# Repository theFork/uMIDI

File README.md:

```
       __  __ _____ _____ _____
      |  \/  |_   _|  __ \_   _|
 _   _| \  / | | | | |  | || |
| | | | |\/| | | | | |  | || |
| |_| | |  | |_| |_| |__| || |_
|  _,_|_|  |_|_____|_____/_____|
| |
|_|
```

The swiss army knife for quick and easy developement of MIDI applications. Possible applications are everything that uses MIDI.

# Documentation
Documentation of hard- and software can be found at https://thefork.github.io/uMIDI/.

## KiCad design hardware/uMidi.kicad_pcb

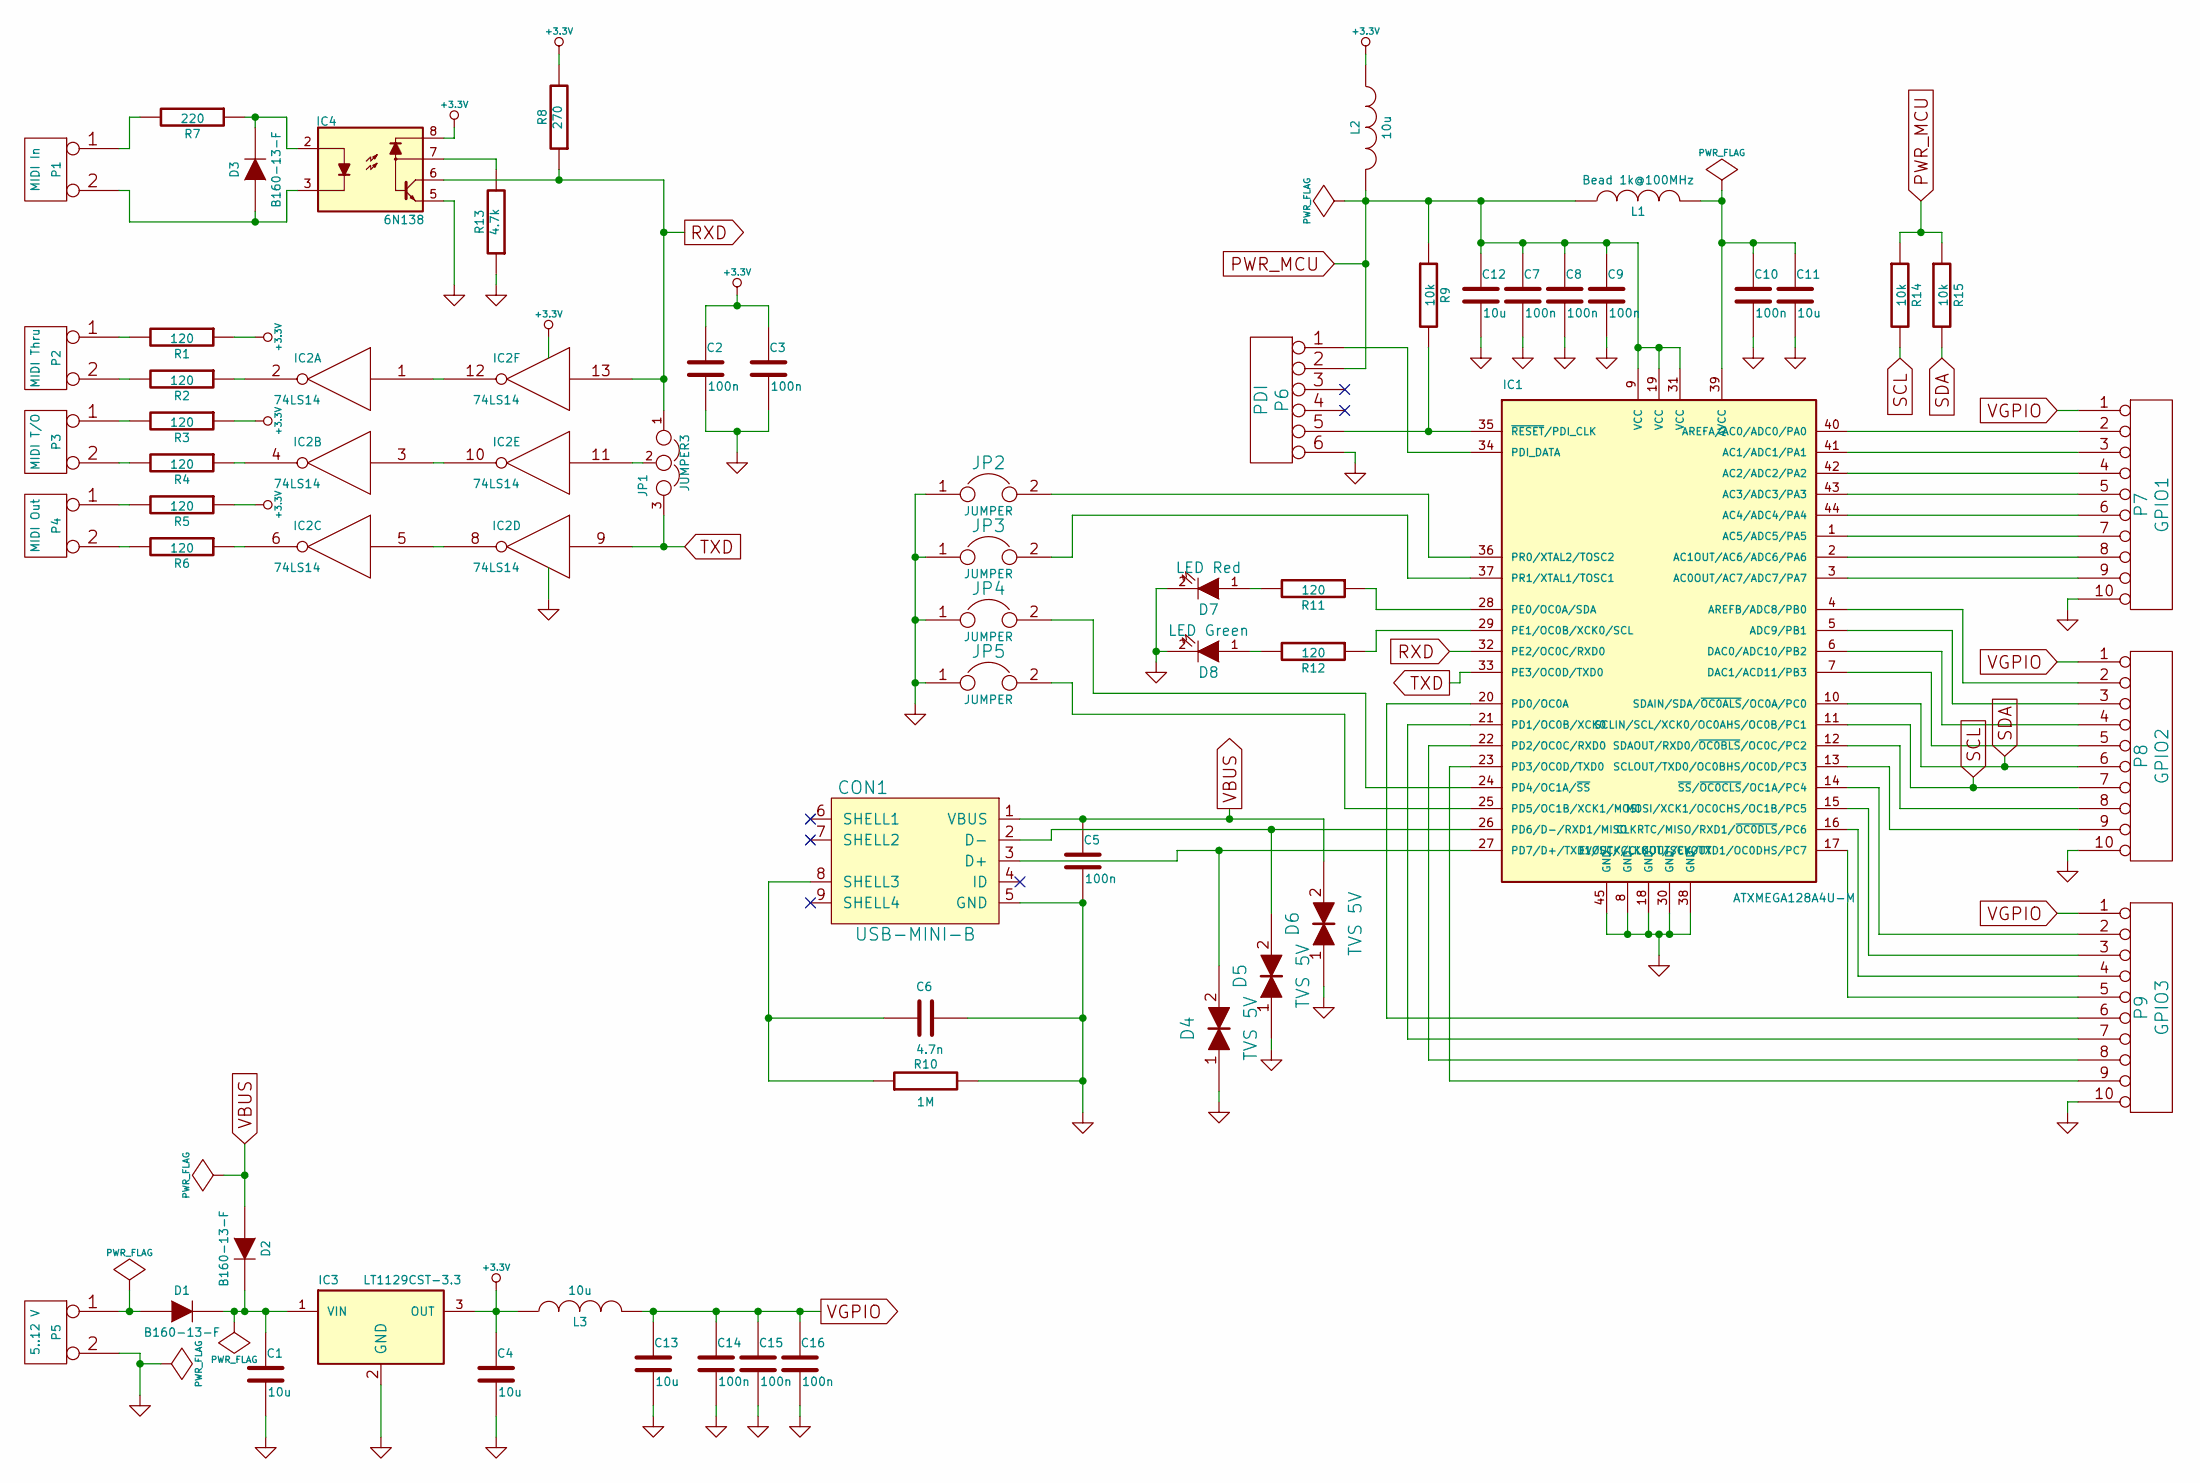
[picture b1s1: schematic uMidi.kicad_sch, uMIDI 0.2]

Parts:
C1, C4, C11, C12, C13: 10u; C_0603; Manufacturer Part Number C0603C106M9PACTU
C2, C3, C5, C7, C8, C9, C10, C14, C15, C16: 100n; C_0603; Manufacturer Part Number CL10B104KB8NNNC
C6: 4.7n; C_0603; Manufacturer Part Number GRM188R71H472KA01D
CON1: USB-MINI-B; Manufacturer Part Number UX60-MB-5ST
D1, D2, D3: B160-13-F; DI-214-AC_SMA; Manufacturer Part Number B160-13-F
D4, D5, D6: TVS 5V; C_0603; Manufacturer Part Number CPDU5V0
D7: LED Red; Manufacturer Part Number LTST-C191KRKT
D8: LED Green; Manufacturer Part Number LTST-C191KGKT
IC1: ATXMEGA128A4U-M; QFN-44-1EP; Manufacturer Part Number ATXMEGA128A4U-MH
IC2: 74LS14; Manufacturer Part Number 74LVT14D,118
IC3: LT1129CST-3.3; SOT-223; Manufacturer Part Number LT1129CST-3.3#PBF
IC4: 6N138; Optocoupler_DIP8_SMD; Manufacturer Part Number 6N138S-TA1
JP1: JUMPER3
JP2, JP3, JP4, JP5: JUMPER
L1: Bead 1k@100MHz; C_0603; Manufacturer Part Number BLM18RK102SN1D
L2, L3: 10u; C_0603; Manufacturer Part Number GLFR1608T100M-LR
P1: MIDI In
P2: MIDI Thru
P3: MIDI T/O
P4: MIDI Out
P5: 5..12 V
P6: PDI; Manufacturer Part Number 67996-206HLF
P7: GPIO1; VASCH5x2; Manufacturer Part Number 30310-6002HB
P8: GPIO2; VASCH5x2; Manufacturer Part Number 30310-6002HB
P9: GPIO3; VASCH5x2; Manufacturer Part Number 30310-6002HB
R1, R2, R3, R4, R5, R6, R11, R12: 120; R_0603; Manufacturer Part Number ERJ-3GEYJ121V
R7: 220; R_0603; Manufacturer Part Number ERJ-3GEYJ221V
R8: 270; R_0603; Manufacturer Part Number ERJ-3GEYJ271V
R9, R14, R15: 10k; R_0603; Manufacturer Part Number ERJ-3GEYJ103V
R10: 1M; R_0603; Manufacturer Part Number ERJ-3GEYJ105V
R13: 4.7k; R_0603; Manufacturer Part Number ERJ-3GEYJ472V

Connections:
+3.3V: C2.1, C3.1, C4.1, IC2.14 (VCC), IC3.3 (OUT), IC4.8, L2.1, L3.1, R1.1, R3.1, R5.1, R8.2
GND: C1.2, C2.2, C3.2, C4.2, C5.2, C6.1, C7.2, C8.2, C9.2, C10.2, C11.2, C12.2, C13.2, C14.2, C15.2, C16.2, CON1.5 (GND), D4.1, D5.1, D6.1, D7.2 (K), D8.2 (K), IC1.8 (GND), IC1.18 (GND), IC1.30 (GND), IC1.38 (GND), IC1.45 (GND), IC2.7 (GND), IC3.2 (GND), IC3.4 (GNDPAD), IC4.5, JP2.1, JP3.1, JP4.1, JP5.1, P5.2 (PM), P6.6, P7.10, P8.10, P9.10, R10.2, R13.1; also elsewhere on the board
unnamed: C1.1, D1.2 (K), D2.2 (K), IC3.1 (VIN)
unnamed: C6.2, CON1.8 (SHELL3), R10.1
unnamed: C10.1, C11.1, IC1.39 (AVCC), L1.2
unnamed: CON1.2 (D-), D5.2, IC1.26 (PD6/D-/RXD1/MISO)
unnamed: CON1.3 (D+), D4.2, IC1.27 (PD7/D+/TXD1/SCK/CLKOUT/EVOUT)
unnamed: D1.1 (A), P5.1
unnamed: D3.1 (A), IC4.3, P1.2 (PM)
unnamed: D3.2 (K), IC4.2, R7.1
unnamed: D7.1 (A), R11.2
unnamed: D8.1 (A), R12.2
unnamed: IC1.1 (AC5/ADC5/PA5), P7.7
unnamed: IC1.2 (AC1OUT/AC6/ADC6/PA6), P7.8
unnamed: IC1.3 (AC0OUT/AC7/ADC7/PA7), P7.9
unnamed: IC1.4 (AREFB/ADC8/PB0), P8.2
unnamed: IC1.5 (ADC9/PB1), P8.3
unnamed: IC1.6 (DAC0/ADC10/PB2), P8.4
unnamed: IC1.7 (DAC1/ACD11/PB3), P8.5
unnamed: IC1.12 (SDAOUT/RXD0/~OC0BLS/OC0C/PC2), P8.8
unnamed: IC1.13 (SCLOUT/TXD0/OC0BHS/OC0D/PC3), P8.9
unnamed: IC1.14 (~SS/~OC0CLS/OC1A/PC4), P9.2
unnamed: IC1.15 (MOSI/XCK1/OC0CHS/OC1B/PC5), P9.3
unnamed: IC1.16 (CLKRTC/MISO/RXD1/~OC0DLS/PC6), P9.4
unnamed: IC1.17 (EVOUT/CLKOUT/SCK/TXD1/OC0DHS/PC7), P9.5
unnamed: IC1.20 (PD0/OC0A), P9.6
unnamed: IC1.21 (PD1/OC0B/XCK0), P9.7
unnamed: IC1.22 (PD2/OC0C/RXD0), P9.8
unnamed: IC1.23 (PD3/OC0D/TXD0), P9.9
unnamed: IC1.24 (PD4/OC1A/~SS), JP4.2
unnamed: IC1.25 (PD5/OC1B/XCK1/MOSI), JP5.2
unnamed: IC1.28 (PE0/OC0A/SDA), R11.1
unnamed: IC1.29 (PE1/OC0B/XCK0/SCL), R12.1
unnamed: IC1.34 (PDI_DATA), P6.1
unnamed: IC1.35 (~RESET/PDI_CLK), P6.5, R9.2
unnamed: IC1.36 (PR0/XTAL2/TOSC2), JP2.2
unnamed: IC1.37 (PR1/XTAL1/TOSC1), JP3.2
unnamed: IC1.40 (AREFA/AC0/ADC0/PA0), P7.2
unnamed: IC1.41 (AC1/ADC1/PA1), P7.3
unnamed: IC1.42 (AC2/ADC2/PA2), P7.4
unnamed: IC1.43 (AC3/ADC3/PA3), P7.5
unnamed: IC1.44 (AC4/ADC4/PA4), P7.6
unnamed: IC2.1, IC2.12
unnamed: IC2.2, R2.1
unnamed: IC2.4, R4.1
unnamed: IC2.5, IC2.8
unnamed: IC2.6, R6.1
unnamed: IC2.3, IC2.10
unnamed: IC2.11, JP1.2
unnamed: IC4.7, R13.2
unnamed: P1.1, R7.2
unnamed: P2.1, R1.2
unnamed: P2.2 (PM), R2.2
unnamed: P3.1, R3.2
unnamed: P3.2 (PM), R4.2
unnamed: P4.1, R5.2
unnamed: P4.2 (PM), R6.2
PWR_MCU: C7.1, C8.1, C9.1, C12.1, IC1.9 (VCC), IC1.19 (VCC), IC1.31 (VCC), L1.1, L2.2, P6.2, R9.1, R14.1, R15.1
RXD: IC1.32 (PE2/OC0C/RXD0), IC2.13, IC4.6, JP1.1, R8.1
SCL: IC1.11 (SCLIN/SCL/XCK0/OC0AHS/OC0B/PC1), P8.7, R14.2
SDA: IC1.10 (SDAIN/SDA/~OC0ALS/OC0A/PC0), P8.6, R15.2
TXD: IC1.33 (PE3/OC0D/TXD0), IC2.9, JP1.3
VBUS: C5.1, CON1.1 (VBUS), D2.1 (A), D6.2
VGPIO: C13.1, C14.1, C15.1, C16.1, L3.2, P7.1, P8.1, P9.1

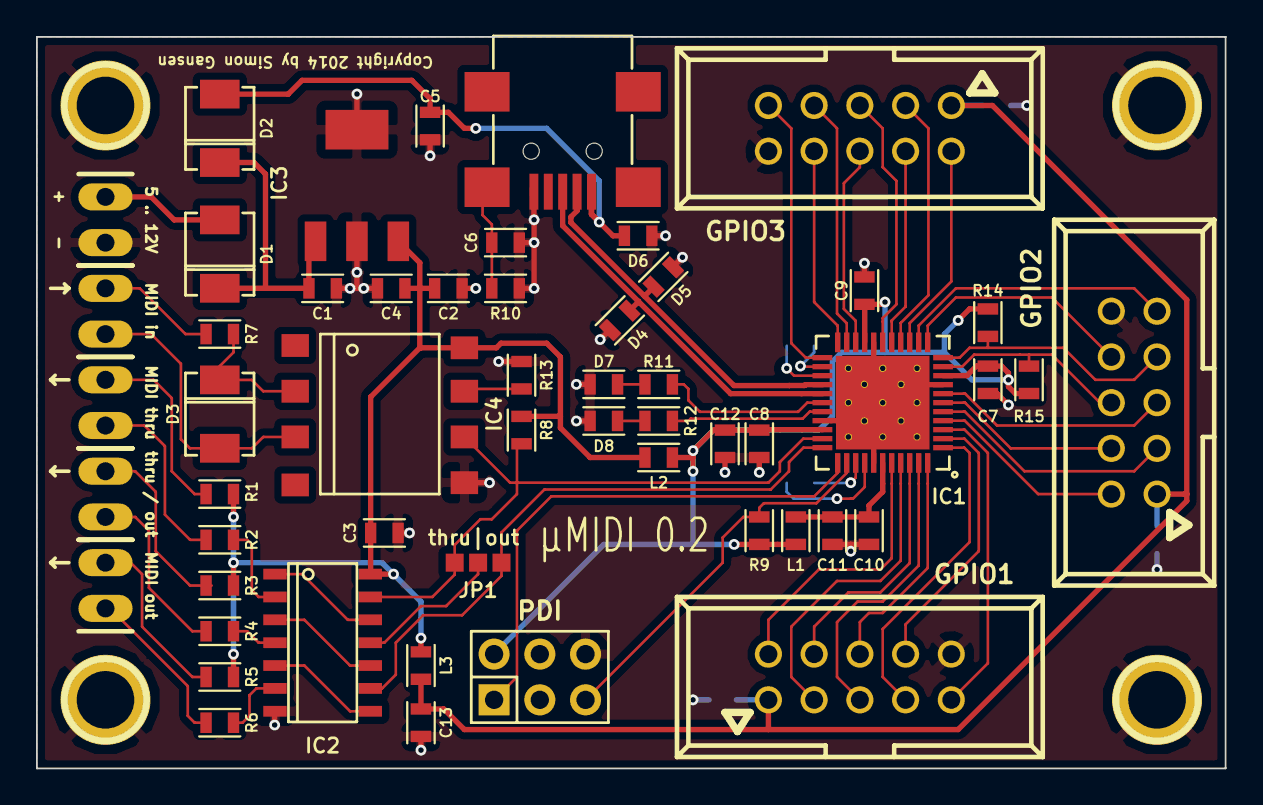
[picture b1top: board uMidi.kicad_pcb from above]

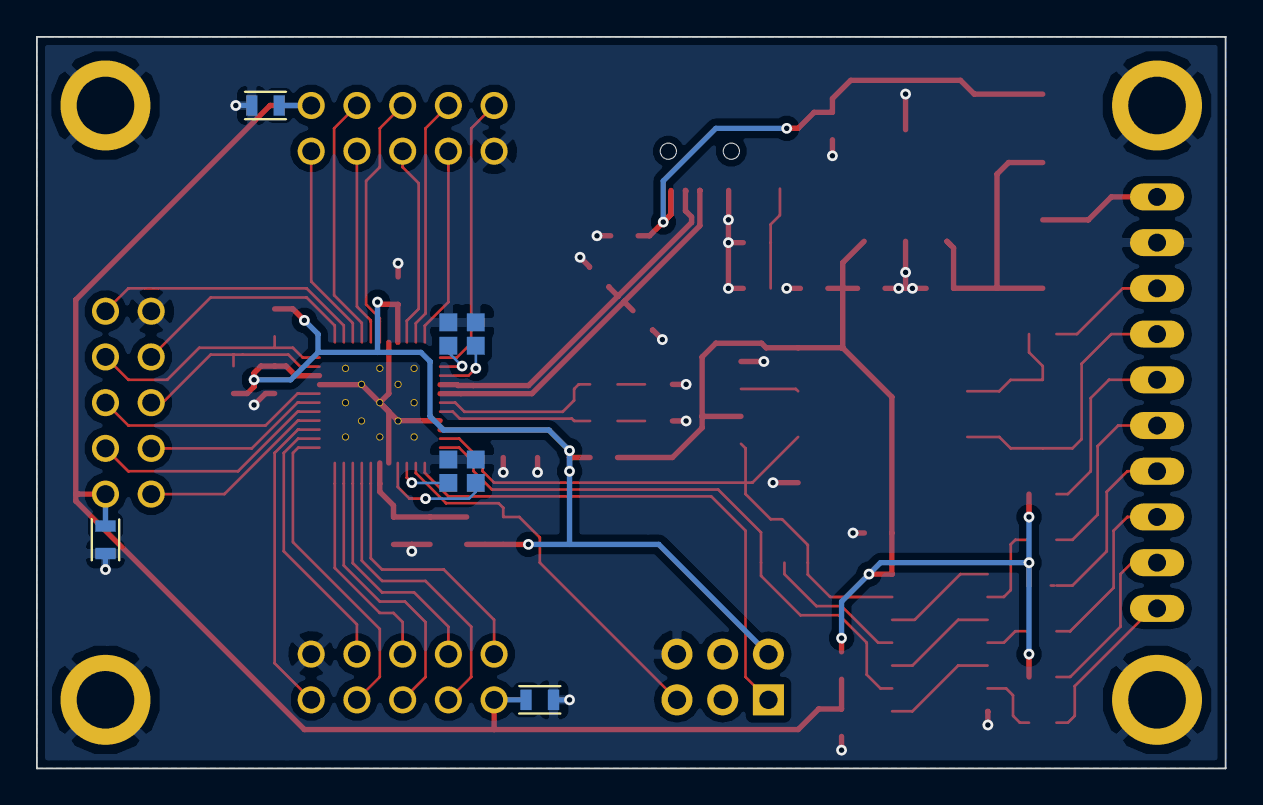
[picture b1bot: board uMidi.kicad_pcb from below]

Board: 2 copper layers, 66.0 x 40.6 mm, 65 parts (7 on the bottom side), 64 nets.

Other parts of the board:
1PIN, 1PIN#2, 1PIN#3, 1PIN#4: P***; 1pin

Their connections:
GND: 1PIN.1, 1PIN#2.1, 1PIN#3.1, 1PIN#4.1; also elsewhere on the board

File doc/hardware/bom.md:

# Bill of Material

## Semiconductors
| Name | Value              | Package       |
|------|--------------------|---------------|
| IC1  | ATXMEGA128A4U-M    | VQFN44        |
| IC2  | 74LS14             |               |
| IC3  | LT1129CST-3.3      | SOT-223       |
| IC4  | 6N138              | SMD-8         |
| D1   | DIODE              |               |
| D2   | DIODE              |               |
| D3   | DIODE              |               |
| D4   | TVS                | 0603          |
| D5   | TVS                | 0603          |
| D6   | TVS                | 0603          |
| D7   | LED, red           | 0603          |
| D8   | LED, green         | 0603          |

## Connectors
| Name | Type               |
|------|--------------------|
| CON1 | USB-MINI-B         |
| P6   | PDI                |
| P7   | GPIO1              |
| P8   | GPIO2              |
| P9   | GPIO2              |

## Passives
| Name | Value              | Package       |
|------|--------------------|---------------|
| R1   | 120                | 0603          |
| R2   | 120                | 0603          |
| R3   | 120                | 0603          |
| R4   | 120                | 0603          |
| R5   | 120                | 0603          |
| R6   | 120                | 0603          |
| R7   | 220                | 0603          |
| R8   | 270                | 0603          |
| R9   | 10k                | 0603          |
| R10  | 1M                 | 0603          |
| R11  | 120                | 0603          |
| R12  | 120                | 0603          |
| R13  | 4.7k               | 0603          |
| R14  | 10k                | 0603          |
| R15  | 10k                | 0603          |
| C1   | 10u                | 0603          |
| C2   | 100n               | 0603          |
| C3   | 100n               | 0603          |
| C4   | 10u                | 0603          |
| C5   | 100n               | 0603          |
| C6   | 4.7n               | 0603          |
| C7   | 100n               | 0603          |
| C8   | 100n               | 0603          |
| C9   | 100n               | 0603          |
| C10  | 100n               | 0603          |
| C11  | 10u                | 0603          |
| C12  | 10u                | 0603          |
| C13  | 10u                | 0603          |
| C14  | 100n               | 0603          |
| C15  | 100n               | 0603          |
| C16  | 100n               | 0603          |
| L1   | Bead               | 0603          |
| L2   | 10u                | 0603          |
| L3   | 10u                | 0603          |

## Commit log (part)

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2016-02-25 Add doxygen software documentation skeleton
2016-02-26 Add missing fuse byte FUSEBYTE0 to Makefiles
2016-03-05 Remove unnecessary whitespace in global Makefile
2016-03-05 Remove unnecessary quotation marks from global Makefile
2016-03-05 Remove onboard LED command
2016-03-06 Complete doxygen mainpage (for now)
2016-03-06 Add initial doxygen documentation
2016-03-06 Remove led debugging; Fix typo; Add doxy comments
2016-03-06 Add switcher documentation page stub
2016-03-06 Add feedback to fwupdate target
2016-03-06 Improve readability of wave functions
2016-03-06 Add activity diagram of the waveform update task
2016-03-06 Implement USB control interface and tap tempo
2016-03-08 Improve GPIO API (see details)
    Applications now need only to provide GPIO pin type configurations for the pins
    they really need. Also there is a new function configure_gpio_pin() that allows
    configuration of pins apart from init_gpio_module().
2016-03-08 Adapt sequencer app to new GPIO API
2016-03-08 Adapt templates to new GPIO API
2016-03-08 Fix warnings in sequencer module due to GPIO API change
2016-03-08 Adapt switcher app to new GPIO API
2016-03-08 Brick sequencer app (see detailed commit message)
    When the GPIO inputs are not properly configured, the function poll_encoder(),
    which is registered as a background task, runs into an endless loop while trying
    to de-bounce the switch. This wakes up the watchdog, which then resets the MCU.
2016-03-12 Document struct jumpers
2016-03-12 Implement generic poll_gpio_input in GPIO module
2016-03-12 Make encoder module capable of handling multiple encoders
2016-03-12 Extract handling of encoder position changes to private function
2016-03-12 Make switch on encoders optional
2016-03-12 Implement HMI module
2016-03-12 Implement 4-phase encoder
2016-03-12 Add reset_wave() to wave module
2016-03-12 Use second encoder to start/stop and select the pattern
2016-03-13 Move wave patterns to program space
2016-03-13 Improve pattern 03
2016-03-13 Make "normal" waveforms accessible
2016-03-14 Generate software version ID string and print it out with the help command
2016-03-14 Refactor sequencer stuff out out whammy app and wave module
2016-03-15 Fix input switch polling
2016-03-16 Clean up sequencer module and fix build
2016-03-16 Roughly specify switcher software
2016-03-19 Prepare for generalized leds
2016-03-19 Implement register_led function
2016-03-19 Fix USB application template
2016-03-19 Convert led.pin to a pointer to a GPIO pin
2016-03-19 Implement flashing save LED on program change
2016-03-19 Implement two blinks on unkown packages and updaet spec
2016-03-19 Implement save switch
2016-03-19 Fix warnings
2016-03-26 Remove datasheets and manuals
2016-03-26 Restructure documentation
2016-03-26 Finish first version of MIDI pinout spec
2016-03-26 Update documentation
2016-03-27 Implement generic send_midi_message()
2016-03-27 Implement proof-of-concept for generalized patterns
2016-03-27 Fix documentation of update_wave()
2016-03-27 Complete implementation of static single-channel sequencer
2016-03-27 Prepare API for multi-channel sequencing
2016-03-27 Remove factory-defined patterns from sequencer module
    These are application-specific and should thus be defined in application code,
    not the library. The Whammy note enumeration is also application-specific and
    therefore moved to the whammy application code as well.
2016-03-27 Implement sequencer clock tick callback
2016-03-27 Move sequencer patterns to EEPROM
2016-03-27 Implement pattern restore from hex-string
2016-03-28 Fix update page size computation
2016-03-28 Wait 2 seconds before saving a program
2016-03-28 Increase verbosity
2016-03-28 Implement export function for programs
2016-03-28 Increase size of serial command buffer
2016-03-28 serial_communication: Use usb_puts() where possible
    This fixes or rather circumvents a bug: When a command in the history is too
    long (larger than about 70 characters) usb_printf() crashes the firmware for
    unknown reasons. Using puts() instead seems to work perfectly fine.
2016-03-28 Implement backup and restore commands
2016-04-03 Fix on-board LEDs
2016-04-03 program.c: Remove debug code from program import
2016-04-03 Completely revert command line-editing "fix"
2016-04-03 Rename program_data.word -> program_data.dword
2016-04-03 Initialize program module with invalid [sic] program number
2016-04-03 Implement sanity checks and return value for import_bank()
2016-04-18 Handle velocity of note off/on messages
2016-04-21 Add a script that creates a full dump of the device
2016-04-21 Modify fuses to enable brown-out detection
2016-04-30 Prepare program_data struct
2016-04-30 Generalize kill-switch; Document program storage
2016-04-30 Handle note messages and toggle selected outputs
2016-04-30 Specify kill switch feature
2016-04-30 Fix program_data raw representation
2016-04-30 Prepare toggle output serial command
2016-04-30 Call note_off handler if velocity is zero
2016-04-30 Tweak wah range once again
2016-04-30 Sort wah module code
2016-04-30 Implement MIDI note on / off command handling
2016-04-30 Disable flashing of red LED on MIDI RX
2016-04-30 Fill in missing MIDI configs in all apps
2016-05-05 Add static power LED
2016-05-05 Refactor status LED: Use LED API
2016-05-06 Fix TX/RX typo; Reduce minimum current requirement
2016-05-07 Fix comment and indentation
2016-05-07 Modify power over midi spec
2016-05-19 serial_communication: Fix memory leak in exec_help
2016-05-20 Add copy and wipe functions for sequencer patterns
2016-05-20 Check if patterns change before writing to EEPROM
2016-05-20 Implement sequencer pattern modification API
2016-05-25 Disable interrupts during ADC offset calibration
2016-05-25 Add linear scaling function int -> midi_value_t
    Also uses fixed point arithmetic for computation of both directions.
2016-05-25 Improve calibration and implement EEPROM storage
2016-05-25 Adapt wah application to changes in the math API
2016-06-24 Cosmetics in main.c of templates
2016-06-25 Implement SPI bit-banging module
2016-06-26 Improve doc on background tasks
2016-06-28 Fix rogue pointer in print_command_from_history()
2016-07-23 Do not overwrite command history with empty lines
2016-07-23 serial_communication: Use simple strtok in exec_help()
2016-07-23 Move lookup tables to program space
2016-07-23 Shrink command history to four commands
2016-07-23 Only transmit CC if status LED is on
2016-07-24 Fix doxygen complaints about supposedly undefined yet documented symbols
2016-07-24 Fix ADC register array
2016-07-25 ADC: Incorporate ADC sample -> MIDI value conversion for ADC channel 0
2016-07-25 Switch to built-in ADC sample -> MIDI value conversion
2016-07-25 Add project-specific vimrc with some settings for the syntastic plugin
2016-11-17 Assign missing footprint
2016-11-17 Swap red and green LEDs according to doc
2016-12-29 HMI: Differentiate between short and long button press events
2016-12-29 program.h: Fix code example
2016-12-29 wave.h: Cosmetics
2016-12-29 Add adjust_program() to program module
2016-12-29 Add program update service function to program module
2016-12-30 config.c: Use MIDI channel enum values
2016-12-30 whammy.c: Make global variables static
2016-12-30 Add factory reset command
2016-12-30 Implement sequencer mode toggle
2016-12-30 Add CLI for pattern modification
2016-12-30 Implement program storage
2016-12-30 Add type definitions for whammy controller program storage
2016-12-30 Handle MIDI program change messages
2016-12-30 Expand dump command to programs
2016-12-30 Expand speed adjustment to all control modes
2016-12-30 Restructure HMI
2016-12-30 Remove obsolete tap tempo button callback
2016-12-30 Implement whammy mode selection
2016-12-30 Do not load a program at startup
2016-12-30 Implement static detune mode
2016-12-30 Implement program selection
2016-12-30 Add ability to update the current program via command line
2017-01-01 Add MIDI sniffer application
2017-01-01 Implement serial command to select the MIDI channel to sniff on
2017-01-01 Remove GPIO configuration
2017-01-01 Explicitly print out USART receiver errors
2017-01-01 Add LED matrix module
2017-01-01 Use LED bar graph module
2017-01-01 Use LED matrix module
2017-01-01 Refactor common stuff out of adafruit display modules
2017-02-25 Divide et impera
    Split the rather huge whammmy module into separate files for the UI (console,
    encoders/buttons and LEDs) and whammy control.
2017-02-25 Use LED matrix instead of HMI LEDs
2017-02-25 Implement display of the program number
2017-02-25 led_matrix: Implement bitmap display helper
2017-02-25 Indicate last changed setting
2017-03-30 Move character display code to LED matrix module
2017-03-30 Re-introduce HMI layers for pattern manipulation
2017-03-30 Separate CLI implementation from main user interface
2017-03-30 Implement pattern length manipulation
2017-03-30 Refactor state variable names
2017-03-30 Implement program copy and wipe
2017-03-30 Add normal and limit mode
2017-03-30 Add possibility to configure interrupts for HMI buttons
2017-03-30 Make use of safe callback wrapper where possible
2017-03-30 Fix background task frequency
2017-03-30 Fix template-nousb build
2017-11-04 Implement command to set the MIDI channel for CC messages
2018-01-22 TESTME: Implement pitch bend mode proof-of-concept
2018-01-22 TESTME: Use shiny new lit buttons
2018-01-22 Always read current setting before flushing the display
2018-01-22 Indicate various events with status LEDs
2018-01-22 Extract MIDI handling routines to separate module
2018-10-28 Generalize PWM module
2018-10-28 Add Wah functionality to Whammy controller
2020-03-26 Tweak syntastic compiler flags
2020-03-26 Configure GitLab CI
2020-03-26 Foward MIDI messages
2021-06-28 Adapt enable switch logic to momentary switch
2022-07-15 LED Matrix: Send buffer only if something has changed
2022-07-15 Improve character Q
2022-07-15 Sequencer: Add manual step function
2022-07-15 impr(Makefile): Nicer software ID for git tags
2022-08-26 Fix missing newlines and typo in docs
2024-04-30 Introduce two foot-switchable modes
2024-04-30 Clarify, that led.h is also useful for external LEDs
2024-04-30 Add cli command for getting both ctrl numbers at once
2024-04-30 chore(switcher): Fix warnings; cosmetics
2024-05-01 chore: Rename .vimrc to .exrc
2024-05-01 impr(expression): Implement mode command and default mode eemem
2024-05-01 Adjust whammy ctrl value when changing range
2024-05-01 PWM: Remove unnecessary include
2024-05-01 Implement pitch bend mode proof-of-concept
2024-05-01 Use shiny new lit buttons
2024-05-01 Implement MIDI control change handling
2024-05-01 Down-size sequencer patterns
2024-05-01 Re-arrange modes
2024-05-01 Set I2C bus speed to 400kHz
2024-05-01 Add include guards for lookup tables + math unit tests
2024-05-01 WIP: Math unit test
2024-05-01 feat(expression): Make enable switch type (momentary/latching) configurable
2024-05-02 Create GitHub CI action for building apps
2024-05-17 Add mounting holes to kicad footprint
2024-06-08 feat(demon): Implement enable command (toggles for now)
2024-06-08 feat(demon): Implement enabling/disabling the device via two outputs
2024-06-08 feat(demon): Implement basic wah PWM
2024-06-08 feat: Adapt to new uMidi demon hardware
2024-06-30 impr: Offset LED PWM min duty
2024-06-30 impr: Blink green LED only during standby
2024-06-30 impr: Tune PWM range
2024-07-01 impr: Toggle wah on short / autowah on long button press
2024-12-02 fix: Correct documentation of mode command; update default mode
2024-12-21 fix(expression): Properly initialize enable switch state
2025-02-14 impr(switcher): Do not flash LED on CC messages
2025-02-24 fix(switcher): Use PSTR for log messages
2025-06-08 Open and save with kicad 9; Update doc
2026-05-25 impr: Update vim configuration (switch to ALE)
2026-05-26 chore(lib/serial_communication.c: Update comment
2026-05-26 clean: Rename wah.dox => demon.dox
2026-05-26 impr: Disable MIDI RX signalling through red LED
2026-05-26 feat: Implement wah PWM min command
2026-05-26 feat: Add command to set PWM max duty attenuation
2026-05-26 chore: Fix typo in function name
2026-05-26 clean(whammy): Drop wah code
2026-05-26 DO NOT MERGE: Explicitly print out USART receiver errors

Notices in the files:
hardware/uMidi.kicad_pcb:
Copyright 2014 by Simon Gansen
